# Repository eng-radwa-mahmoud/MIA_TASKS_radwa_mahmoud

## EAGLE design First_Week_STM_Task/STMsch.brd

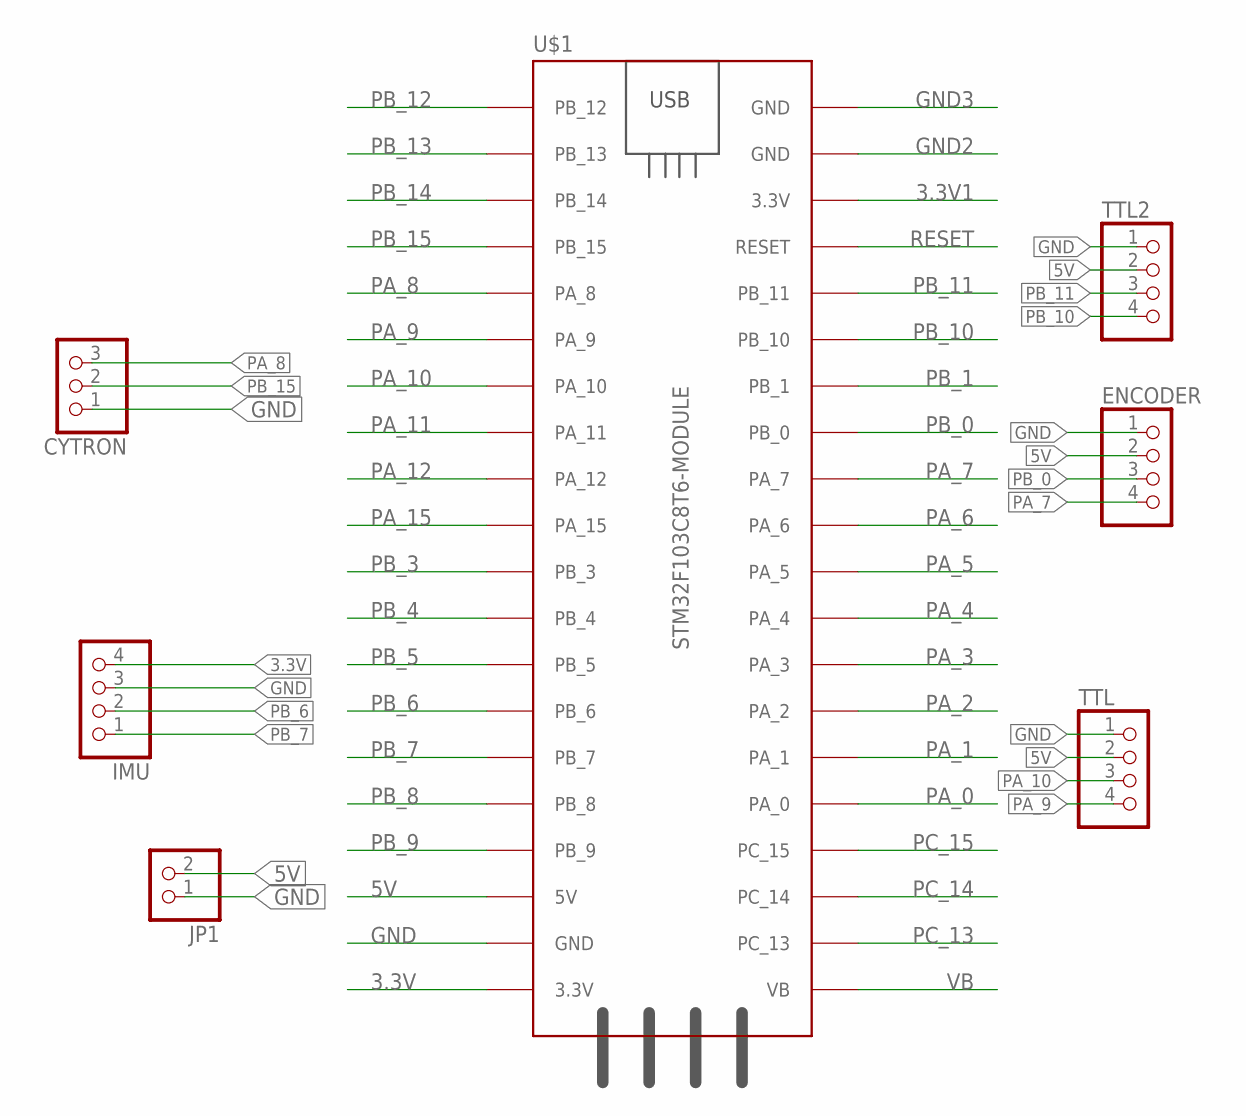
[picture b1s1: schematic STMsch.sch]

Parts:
CYTRON: PINHD-3_DATA; 1X03_DATA
ENCODER: PINHD-4_DATA; 1X04_DATA
IMU: PINHD-1X4; 1X04
JP1: PINHD-2_DATA; 1X02_DATA
TTL, TTL2: PINHD-4_DATA; 1X04_DATA
U$1: STM32F103C8T6-MODULE

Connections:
3.3V: IMU.4, U$1.3.3V_1 (3.3V)
3.3V1: U$1.3.3V_2 (3.3V)
5V: ENCODER.2, JP1.2, TTL.2, TTL2.2, U$1.5V
GND: CYTRON.1, ENCODER.1, IMU.3, JP1.1, TTL.1, TTL2.1, U$1.GND_1 (GND)
GND2: U$1.GND_2 (GND)
GND3: U$1.GND_3 (GND)
PA_0: U$1.PA_0
PA_1: U$1.PA_1
PA_2: U$1.PA_2
PA_3: U$1.PA_3
PA_4: U$1.PA_4
PA_5: U$1.PA_5
PA_6: U$1.PA_6
PA_7: ENCODER.4, U$1.PA_7
PA_8: CYTRON.3, U$1.PA_8
PA_9: TTL.4, U$1.PA_9
PA_10: TTL.3, U$1.PA_10
PA_11: U$1.PA_11
PA_12: U$1.PA_12
PA_15: U$1.PA_15
PB_0: ENCODER.3, U$1.PB_0
PB_1: U$1.PB_1
PB_3: U$1.PB_3
PB_4: U$1.PB_4
PB_5: U$1.PB_5
PB_6: IMU.2, U$1.PB_6
PB_7: IMU.1, U$1.PB_7
PB_8: U$1.PB_8
PB_9: U$1.PB_9
PB_10: TTL2.4, U$1.PB_10
PB_11: TTL2.3, U$1.PB_11
PB_12: U$1.PB_12
PB_13: U$1.PB_13
PB_14: U$1.PB_14
PB_15: CYTRON.2, U$1.PB_15
PC_13: U$1.PC_13
PC_14: U$1.PC_14
PC_15: U$1.PC_15
RESET: U$1.RESET
VB: U$1.VB

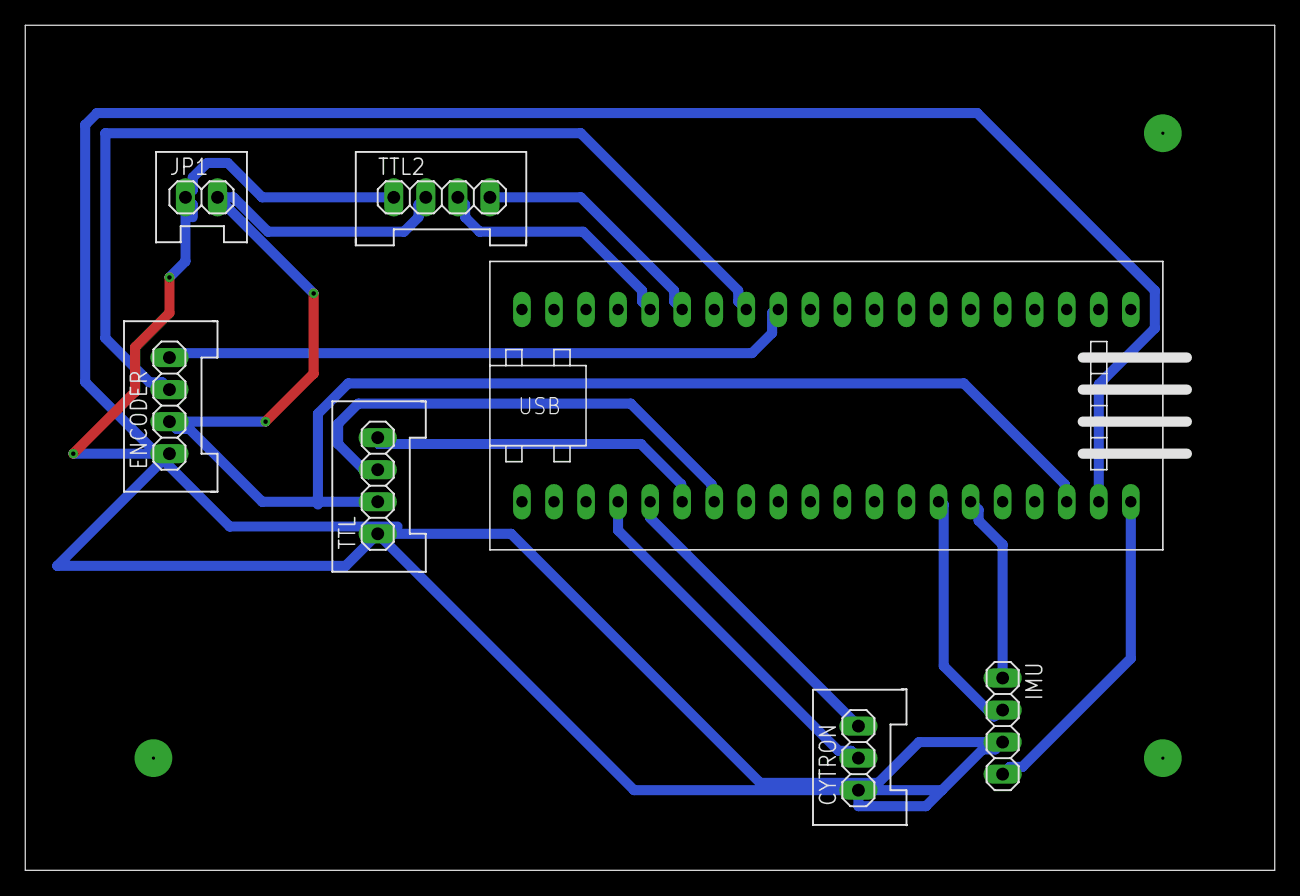
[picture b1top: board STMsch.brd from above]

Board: 2 copper layers, 99.0 x 67.0 mm, 7 parts (0 on the bottom side), 13 nets.

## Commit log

2021-11-02 CODE
2021-11-09 Control
